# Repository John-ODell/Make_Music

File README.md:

Making Music with passive Buzzers by John O'Dell
--Update-- 12/4/2024 -> New Synth Update, Scroll Below for instructions. 

Arduino_Scale_Example

Items needed

    - Arduino uno (tested on r4)
    - Raspbery Pi Pico (Test on Pi Pico 2)
    - Passive buzzer module (two preffered and used in sketch)
    - Jumper Wire

Pin Outs

Buzzer 1
    - signal -> Pin 2
    - GND -> GND
    - VCC -> 3.3v

Buzzer 2

    - signal -> Pin 3
    - GND -> GND
    - VCC -> 3.3v

Download the Arduino IDE Platform https://www.arduino.cc/en/software

Open the sketch "arduino_scale_example"

    - Compile and write to your device
    - On Buzzer one C major scale with play with half notes in two onvtices
    - On Buzzer two C major scale will play with Whole notes in two octives

Python Example

Pin Outs

Buzzer 1
    - signal -> Pin 20
    - GND -> GND
    - VCC -> 3.3v

Buzzer 2

    - signal -> Pin 19
    - GND -> GND
    - VCC -> 3.3v

Download the Thonny IDE Platform https://thonny.org/
    
** Follow the Flash Instructions Below To install Micropython onto your Device **

Open the sketch "passive_buzzer_music_test"

    - Press the green arrow
    - On Buzzer one C major scale with play with half notes in two onvtices
    - On Buzzer two C major scale will play with Whole notes in two octives

TROUBLESHOOTING

    - Make sure that your wires are correct for sketch
    - You may get feedback from just signal wires, make sure vcc and ground are in
    - keep to 3.3v on the arduino
    - Some buzzer modules are not good enough quality
    - to increase or quite the noise, change the duty cycle
    - notation is based off 440A and modern tunings. 

** Flashing MicroPython **

    - Open Thonny
    - Navigate to the top left
     - click run
      - configure interpreter 
      - on the bottom right
        - install Micropython
            - Target Volume will be chosen
            - Micrpython Family (RP2 for Raspberry Pi/Your device Family)
            - Variant (Check the Manufacturer)
            - Version, Most recent
            - Install
    - Afer the flash is done exit out of the Interpreter Pages
    - Click on run again
        - Configuer Interpreter
        - "Which Kind of INterpreter should Thonny use"
            - Micropython for your model device (some models will be automatically dedectied)
        - "Port or WebREPL"
            - COMS(number)
            - This number may have changed from when you ran through this the first time.
            - Click Ok
    - On the Thonny home page, Click the Red stop Sign
    - In the Shell below, You will see your device.

---- Pi Pico Synth - 10 Key Bread Board Synth by John O'Dell ----
Updated 12/4/2024

Items needed

    - 10 Touch Input models (feel free to change the inputs, I found touch to be the best for input time, 10 inputs needed)
    - 2 Passive Buzzers (based on how loud you want your Synth to be)
    - Pi Pico 2 with Micropython
    - Thonny IDE
    - ~40 Jumper Wires
    - 2 Breadboards (Recommended for Button Placement but can be done with 1)

This Sketch requires your inputs to be accesseble at all times, please think about how you are wiring so there are not any false inputs.

Pin Outs 

    - All Modules will use a common 3.3v and GND
    - It is easiest to "pick a side" for each module
        - Touch inputs
            - VCC -> 3.3v
            - GND -> GND
            - S -> GPIO 16 - GPIO 22, GPIO 26-28 
                - 10 sequintial pins for easy orginization
        - Passive Buzzers
            - VCC -> 3.3v
            - GND -> GND
            - S -> GPIO 12 - GPIO 13
                - 2 sequintal pins for two buzzers, add more for more sound. I found two is good for personal playing.

Touch Button Example

This example is to make sure your inputs are working

    - open "touch_button.py" and press the green arrow
    - when you press a button in the serial monitor it will return a button has been pressed
    - Change the Pin number in the top the check if all your buttons are working

TROUBLESHOOTING

    - Make Sure you have not switched the VCC and the GND
    - The number is not the pin number but eh GPIO number, refer to the Raspberr Pi Pico pinout sheet

8 Key example

In this example We use 8 touch buttons and turn them into the "White keys" of a piano by assigning them each to a note of the C major scale.
We anchor this tuning based on A4 (fourth octive) at A 440hz. From this we can find the tuning of our different keys. We have a high sample rate for self regulation of Timing rather than a set BPM

    - Open "8_key.py" and press the green arrow
    - starting with the input assigned to GPIO 16, we play a major C scale.
    - In the serial monitor there will be a high refresh rate showing when a button is pressed along with the frequency associated with it

TROUBLESHOOTING

    - make sure you have VCC and GND correct
    - Make sure you are in the Correct GPIO pins
    - if wired in parrallel, there could be a power issue, wiring pin for pin I found has a better sound

--- Pi Pico Synth by John O'Dell ----

This is a mini Synth that has uses 10 touch inputs with passive buzzers to achieve two full ovtives of a piano/synth. 
8 Inputs are assigned the me C major scale, with one Input raising them a half step and another raising them an octive.
This is a fun exmperimental instrument that has a particular 8 bit sound to it.

    - Follow the main wiring diagram 
    - Open "mod_8_key.py" and press the green arrow
        - to play on boot, save the file to the Pi Pico device and name it "boot.py"
            - to get out of a boot cycle, refer to the  **Flashing MicroPython** Section
    
    - Feel Free to change the assigned tones to the keys to make a new set scale.
    - The modulating buttons can be changed as well in their current function, or a totally new one.
    
Practice Song:

    - (refer the the GPIO Pins)
        - |16 18 20|16 18 20|17 19 21|17 19 21|17 19 22|17 19 22|19 21 26|19 21 26|
    - (Refer to the Notes)
        -|C E G| C E G| D F A| D F A| D F B| D F B| E A C| E A C|

## PCB development

The first battery-powered Pico carrier is now an editable, routed KiCad project with removable Pico H sockets, ten touch controls, two buzzer module connectors and GPIO expansion. Electrical/board checks pass; exact-part fit, mechanical CAD and bench validation still hold fabrication. See [hardware/README.md](hardware/README.md) for the project and held review files.

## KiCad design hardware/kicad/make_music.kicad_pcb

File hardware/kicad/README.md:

# Editable Pico instrument carrier

Open `make_music.kicad_pro` in KiCad 10, then open the schematic. The project-local `MakeMusic.kicad_sym` library and `sym-lib-table` resolve all symbols. `fp-lib-table` registers socket, carrier and power libraries plus installed KiCad 10 `Connector_JST`, `Resistor_SMD`, `Capacitor_SMD` and `TestPoint` libraries. The schematic is the editable source of truth; do not regenerate it from the review PDF.

- `make_music.kicad_sch`: A3 root with two removable female sockets, ten touch/two buzzer cable headers, expansion, two reset pull-ups, twelve 100nF header bypass capacitors and C17/C18 10µF buzzer bulk capacitors.
- `battery_power.kicad_sch`: editable A3 child sheet with JST battery entry, upstream fuse, switch, TPS259474L protection and supporting passives/clamps; VSYS/GND connect through hierarchical ports.
- `make_music.kicad_pcb`: routed 48-part electrical carrier with 17 mounting holes, two ground pours and module/cassette references. C17/C18 and corrected 18650/H1 routing are integrated. Current checks and retained metadata warnings are in [PCB status](PCB_STATUS.md).
- `schematic-review.pdf`: readable two-page A3 schematic export, marked prototype review.
- `pico-socket-map.csv`: all 40 Pico physical pins mapped to local socket pins and carrier nets.
- `verify_connectivity.py`: checks every endpoint in a fresh XML netlist against the reviewed interface contract.
- `carrier-interfaces.md`: exact carrier parts, cable mapping, footprint evidence and placement/release gates.
- `power-integration.md`: native reference mapping, power parts, RPW/fuse/TVS geometry, validation and qualification gates.
- `../reviews/schematic.md`: verified facts, actual checks and unresolved design decisions.

J1 and J2 each use local pad numbers 1-20. J1 pin 1 is at the USB end; J2 pin 1 is at the opposite end. J2 pin 20 is beside USB. J1/J2 are assigned `MakeMusic:Samtec_SSQ-120-01-G-S_1x20_P2.54mm` as candidates. Place J1 pad 1 at USB and rotate J2 180 degrees relative to J1 so J2 pad 20 is at USB. This integration numbering supersedes the mechanical proposal's alternative right-row pad-1-at-USB convention; do not reverse the existing schematic nets to match that proposal.

J3-J14 carrier order is defined as 1=SIG, 2=3V3_OUT, 3=GND. Assigned Harwin headers are cable adapters; actual module pin order is mapped separately by label, and no module mounting geometry is claimed. J15 has the exact Harwin 16-way candidate and defined GPIO order. H1 is the underside JST PH battery harness, circuit1=BAT_PROT_PLUS/circuit2=GND; it does not put holder contacts or holes on the carrier. All **48 schematic physical components** have assigned footprints: **47 purchased parts** plus TP1's 2mm bare copper test pad. J1/J2 now store native SSQ-120-01-G-S MPN and Samtec datasheet fields; supplier BOMs need no socket-identity substitution. See [carrier interface contract](carrier-interfaces.md) for ST0238 cable permutation, reset bias, bulk-capacitor land evidence and local bypass placement. The selected inserted module is original non-wireless RP2040 Pico H SC0917 with fitted male headers; its electronics and the module drivers remain off-board/unmodeled. Cold-fit/engagement checks remain. The updated schematic passes native ERC with zero errors/warnings and the 166-endpoint contract; live PCB pad/identity checks now agree; four custom-field warnings remain reported.

Run from this directory (write generated logs/netlists outside the repository):

```sh
kicad-cli sch erc --severity-all --exit-code-violations --format json -o /tmp/make-music-erc.json make_music.kicad_sch
kicad-cli sch export netlist --format kicadxml -o /tmp/make-music-netlist.xml make_music.kicad_sch
python3 verify_connectivity.py /tmp/make-music-netlist.xml
kicad-cli sch export pdf -o schematic-review.pdf make_music.kicad_sch
```

The user permits firmware adaptation to confirmed touch polarity, including active-low. Confirm direct/momentary configuration and actual idle/touched levels first; the separate carrier_prototype.py firmware supports configurable active levels; no module polarity has been measured.

Revision-1 source path: protected-cell external + -> H1 circuit1 -> F1 -> BAT_FUSED_PLUS -> S1 common2; S1 throw3 -> BAT_SW_PLUS -> U2 IN5; U2 OUT6 -> VSYS/Pico physical39. S1 throw1 is NC (battery OFF). H1 circuit2 joins GND. Carrier series D1 is removed. D2 is a VSYS-to-GND shunt clamp; D3 is the bidirectional input TVS. TP1 only joins USB VBUS/Pico physical40. The Pico's internal USB diode/regulator remain off-board. See [native power integration](power-integration.md) for exact R3–R8/C13–C16 mapping and package evidence.

Battery OFF permits USB power. Remove the cell for external charging; no onboard charger is present. Source changes may reboot: stop playing and let the instrument restart before resuming. No polymer hold-up additions are fitted. Hardware UVLO/overload protection is implemented, while assembly-specific protection response, PCM thresholds, actual cell/holder fit and power/load/thermal validation remain open. Adopted limits are ≤0.70A battery branch, ≤350mA total3V3 including Pico, ≤250mA external3V3 and ≤100µF total VSYS capacitance including Pico. The user corrected the battery format to **18650** on 2026-10-09; the primary power/mechanical review owns updated exact cell/holder/charger choices. R1/R2 bias GP13/12 HIGH while pins are high impedance; firmware must idle HIGH and ST0238 startup/current/PWM still need testing. C1–C12 remain100nF at the carrier headers; native C5/C6 are retained and are unrelated to the removed power-document polymer C5/C6. C17/C18 add 10µF each at J13/J14 on 3V3_OUT; qualify effective capacitance and 3V3 startup/inrush.

The current held package includes C17/C18 and the corrected long18650
cassette/H1 move. Electrical integration and saved/refilled checks agree with
the source-bound exports. Native parity retains four metadata warnings; actual
pad nets, values and full footprint IDs agree. All drawing pages and actual
Gerber/drill whole/detail reviews are recorded. Current findings are in
PCB_STATUS.md. Complete exact-part fit, final mechanical CAD, bench/thermal
qualification and factory acceptance before manufacturing release. See
../assembly/FIT_CHECKLIST.md and ../manufacturing/README.md. The retired
export_review.py refuses to run; native exports use Konnect MCP.

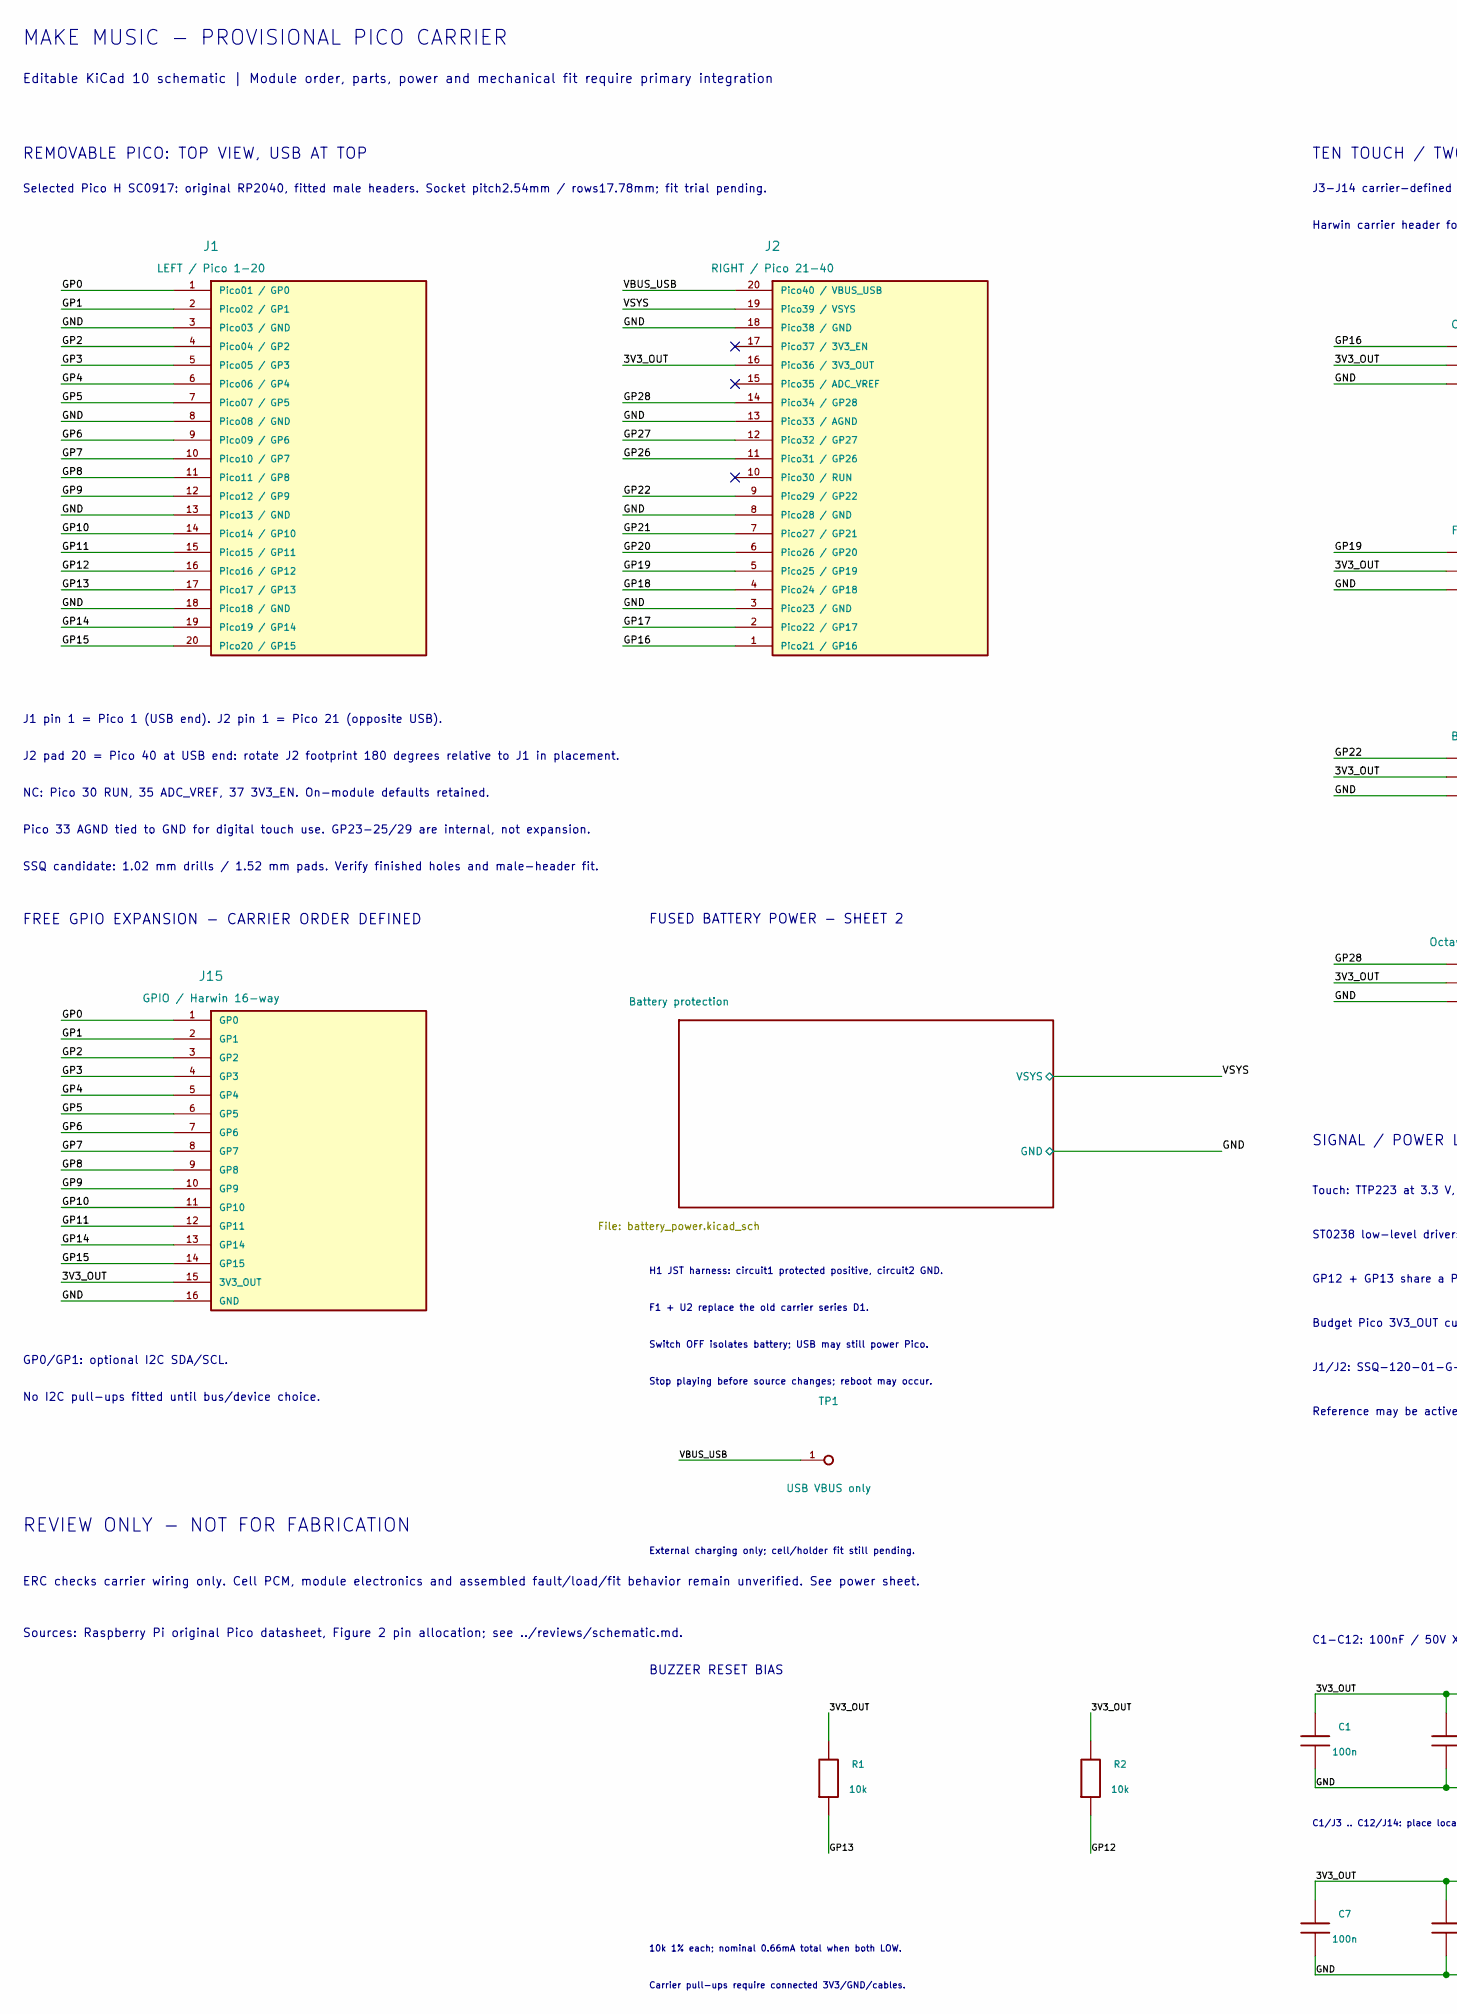
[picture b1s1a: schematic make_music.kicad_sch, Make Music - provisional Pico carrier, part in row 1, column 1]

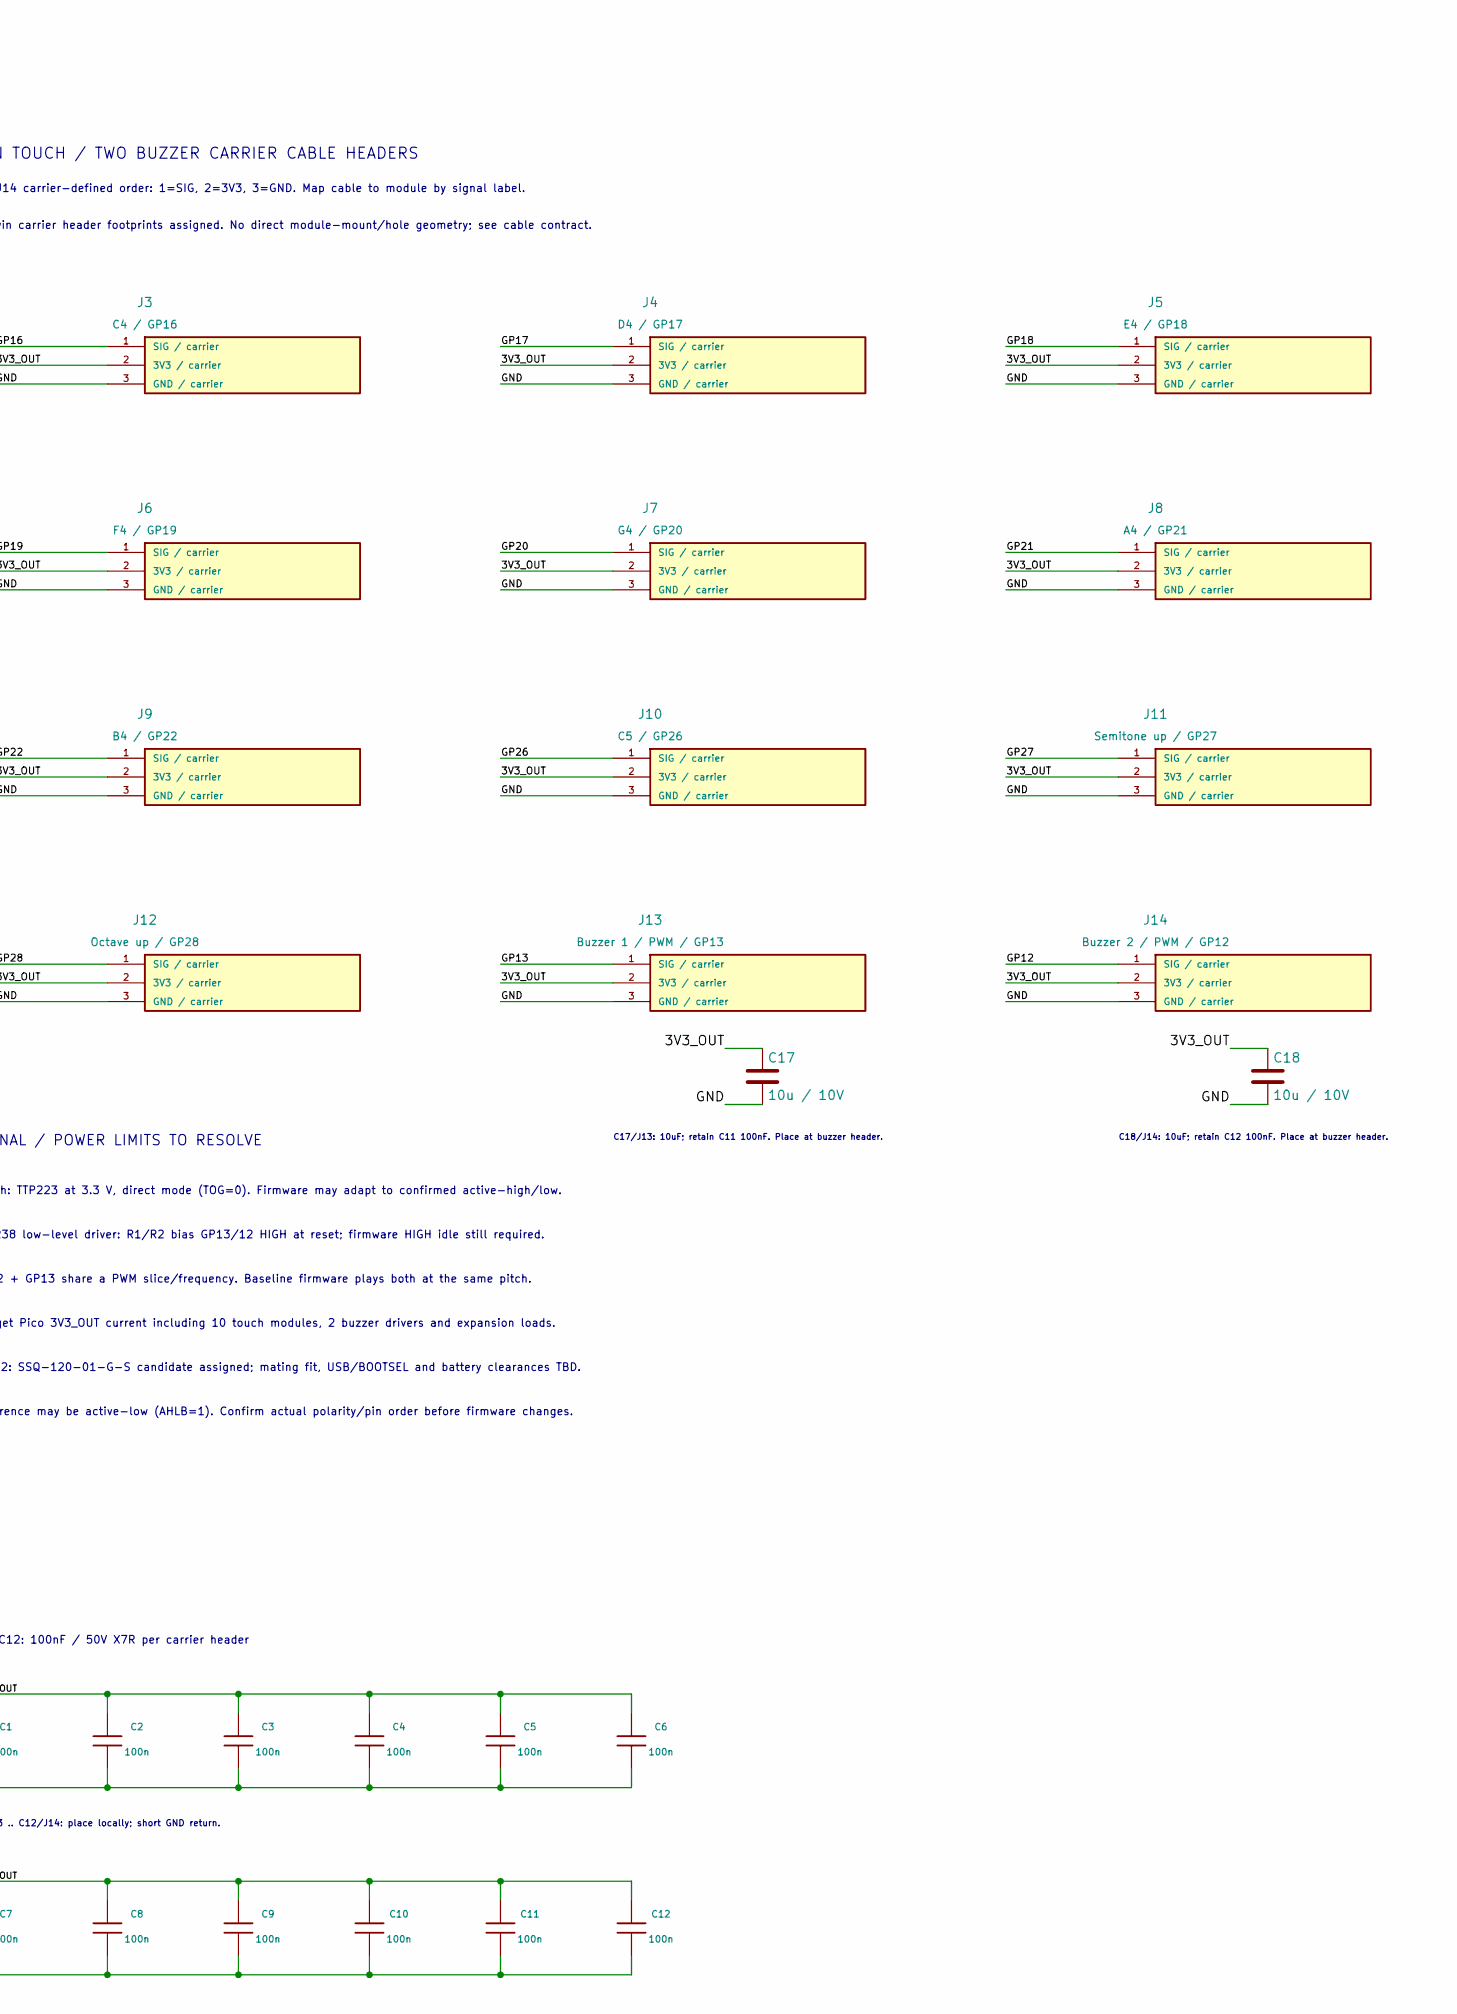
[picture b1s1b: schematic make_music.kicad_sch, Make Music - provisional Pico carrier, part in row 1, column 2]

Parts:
C1, C2, C3, C4, C5, C6, C7, C8, C9, C10, C11, C12: 100n; KEMET_C0603_1608_LevelB; MPN C0603C104K5RACTU
C17, C18: 10u / 10V; C_0805_2012Metric; MPN C2012X7R1A106K125AC
J1: LEFT / Pico 1-20; Samtec_SSQ-120-01-G-S_1x20_P2.54mm; MPN SSQ-120-01-G-S
J2: RIGHT / Pico 21-40; Samtec_SSQ-120-01-G-S_1x20_P2.54mm; MPN SSQ-120-01-G-S
J3: C4 / GP16; Harwin_M20-9990346_1x3_P2.54mm; MPN M20-9990346
J4: D4 / GP17; Harwin_M20-9990346_1x3_P2.54mm; MPN M20-9990346
J5: E4 / GP18; Harwin_M20-9990346_1x3_P2.54mm; MPN M20-9990346
J6: F4 / GP19; Harwin_M20-9990346_1x3_P2.54mm; MPN M20-9990346
J7: G4 / GP20; Harwin_M20-9990346_1x3_P2.54mm; MPN M20-9990346
J8: A4 / GP21; Harwin_M20-9990346_1x3_P2.54mm; MPN M20-9990346
J9: B4 / GP22; Harwin_M20-9990346_1x3_P2.54mm; MPN M20-9990346
J10: C5 / GP26; Harwin_M20-9990346_1x3_P2.54mm; MPN M20-9990346
J11: Semitone up / GP27; Harwin_M20-9990346_1x3_P2.54mm; MPN M20-9990346
J12: Octave up / GP28; Harwin_M20-9990346_1x3_P2.54mm; MPN M20-9990346
J13: Buzzer 1 / PWM / GP13; Harwin_M20-9990346_1x3_P2.54mm; MPN M20-9990346
J14: Buzzer 2 / PWM / GP12; Harwin_M20-9990346_1x3_P2.54mm; MPN M20-9990346
J15: GPIO / Harwin 16-way; Harwin_M20-9991646_1x16_P2.54mm; MPN M20-9991646
R1, R2: 10k; R_0603_1608Metric; MPN RC0603FR-0710KL
TP1: USB VBUS only; TestPoint_Pad_D2.0mm

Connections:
/3V3_OUT: C1.1, C2.1, C3.1, C4.1, C5.1, C6.1, C7.1, C8.1, C9.1, C10.1, C11.1, C12.1, C17.1, C18.1, J2.16 (Pico36 / 3V3_OUT), J3.2 (3V3 / carrier), J4.2 (3V3 / carrier), J5.2 (3V3 / carrier), J6.2 (3V3 / carrier), J7.2 (3V3 / carrier), J8.2 (3V3 / carrier), J9.2 (3V3 / carrier), J10.2 (3V3 / carrier), J11.2 (3V3 / carrier), J12.2 (3V3 / carrier), J13.2 (3V3 / carrier), J14.2 (3V3 / carrier), J15.15 (3V3_OUT), R1.1, R2.1
/GND: C1.2, C2.2, C3.2, C4.2, C5.2, C6.2, C7.2, C8.2, C9.2, C10.2, C11.2, C12.2, C17.2, C18.2, J1.3 (Pico03 / GND), J1.8 (Pico08 / GND), J1.13 (Pico13 / GND), J1.18 (Pico18 / GND), J2.3 (Pico23 / GND), J2.8 (Pico28 / GND), J2.13 (Pico33 / AGND), J2.18 (Pico38 / GND), J3.3 (GND / carrier), J4.3 (GND / carrier), J5.3 (GND / carrier), J6.3 (GND / carrier), J7.3 (GND / carrier), J8.3 (GND / carrier), J9.3 (GND / carrier), J10.3 (GND / carrier), J11.3 (GND / carrier), J12.3 (GND / carrier), J13.3 (GND / carrier), J14.3 (GND / carrier), J15.16 (GND); also elsewhere on the board
/GP0: J1.1 (Pico01 / GP0), J15.1 (GP0)
/GP1: J1.2 (Pico02 / GP1), J15.2 (GP1)
/GP2: J1.4 (Pico04 / GP2), J15.3 (GP2)
/GP3: J1.5 (Pico05 / GP3), J15.4 (GP3)
/GP4: J1.6 (Pico06 / GP4), J15.5 (GP4)
/GP5: J1.7 (Pico07 / GP5), J15.6 (GP5)
/GP6: J1.9 (Pico09 / GP6), J15.7 (GP6)
/GP7: J1.10 (Pico10 / GP7), J15.8 (GP7)
/GP8: J1.11 (Pico11 / GP8), J15.9 (GP8)
/GP9: J1.12 (Pico12 / GP9), J15.10 (GP9)
/GP10: J1.14 (Pico14 / GP10), J15.11 (GP10)
/GP11: J1.15 (Pico15 / GP11), J15.12 (GP11)
/GP12: J1.16 (Pico16 / GP12), J14.1 (SIG / carrier), R2.2
/GP13: J1.17 (Pico17 / GP13), J13.1 (SIG / carrier), R1.2
/GP14: J1.19 (Pico19 / GP14), J15.13 (GP14)
/GP15: J1.20 (Pico20 / GP15), J15.14 (GP15)
/GP16: J2.1 (Pico21 / GP16), J3.1 (SIG / carrier)
/GP17: J2.2 (Pico22 / GP17), J4.1 (SIG / carrier)
/GP18: J2.4 (Pico24 / GP18), J5.1 (SIG / carrier)
/GP19: J2.5 (Pico25 / GP19), J6.1 (SIG / carrier)
/GP20: J2.6 (Pico26 / GP20), J7.1 (SIG / carrier)
/GP21: J2.7 (Pico27 / GP21), J8.1 (SIG / carrier)
/GP22: J2.9 (Pico29 / GP22), J9.1 (SIG / carrier)
/GP26: J2.11 (Pico31 / GP26), J10.1 (SIG / carrier)
/GP27: J2.12 (Pico32 / GP27), J11.1 (SIG / carrier)
/GP28: J2.14 (Pico34 / GP28), J12.1 (SIG / carrier)
/VBUS_USB: J2.20 (Pico40 / VBUS_USB), TP1.1
/VSYS: J2.19 (Pico39 / VSYS); also elsewhere on the board

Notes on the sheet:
MAKE MUSIC - PROVISIONAL PICO CARRIER
Editable KiCad 10 schematic | Module order, parts, power and mechanical fit require primary integration
REMOVABLE PICO: TOP VIEW, USB AT TOP
Selected Pico H SC0917: original RP2040, fitted male headers. Socket pitch2.54mm / rows17.78mm; fit trial pending.
J1 pin 1 = Pico 1 (USB end). J2 pin 1 = Pico 21 (opposite USB).
J2 pad 20 = Pico 40 at USB end: rotate J2 footprint 180 degrees relative to J1 in placement.
NC: Pico 30 RUN, 35 ADC_VREF, 37 3V3_EN. On-module defaults retained.
Pico 33 AGND tied to GND for digital touch use. GP23-25/29 are internal, not expansion.
FREE GPIO EXPANSION - CARRIER ORDER DEFINED
GP0/GP1: optional I2C SDA/SCL.
No I2C pull-ups fitted until bus/device choice.
TEN TOUCH / TWO BUZZER CARRIER CABLE HEADERS
J3-J14 carrier-defined order: 1=SIG, 2=3V3, 3=GND. Map cable to module by signal label.
Harwin carrier header footprints assigned. No direct module-mount/hole geometry; see cable contract.
SIGNAL / POWER LIMITS TO RESOLVE
Touch: TTP223 at 3.3 V, direct mode (TOG=0). Firmware may adapt to confirmed active-high/low.
ST0238 low-level driver: R1/R2 bias GP13/12 HIGH at reset; firmware HIGH idle still required.
GP12 + GP13 share a PWM slice/frequency. Baseline firmware plays both at the same pitch.
Budget Pico 3V3_OUT current including 10 touch modules, 2 buzzer drivers and expansion loads.
J1/J2: SSQ-120-01-G-S candidate assigned; mating fit, USB/BOOTSEL and battery clearances TBD.
REVIEW ONLY - NOT FOR FABRICATION
ERC checks carrier wiring only. Cell PCM, module electronics and assembled fault/load/fit behavior remain unverified. See power sheet.
Sources: Raspberry Pi original Pico datasheet, Figure 2 pin allocation; see ../reviews/schematic.md.
Reference may be active-low (AHLB=1). Confirm actual polarity/pin order before firmware changes.
SSQ candidate: 1.02 mm drills / 1.52 mm pads. Verify finished holes and male-header fit.
BUZZER RESET BIAS
10k 1% each; nominal 0.66mA total when both LOW.
Carrier pull-ups require connected 3V3/GND/cables.
C1-C12: 100nF / 50V X7R per carrier header
C1/J3 .. C12/J14: place locally; short GND return.
FUSED BATTERY POWER - SHEET 2
H1 JST harness: circuit1 protected positive, circuit2 GND.
F1 + U2 replace the old carrier series D1.
Switch OFF isolates battery; USB may still power Pico.
Stop playing before source changes; reboot may occur.
External charging only; cell/holder fit still pending.
C17/J13: 10uF; retain C11 100nF. Place at buzzer header.
C18/J14: 10uF; retain C12 100nF. Place at buzzer header.

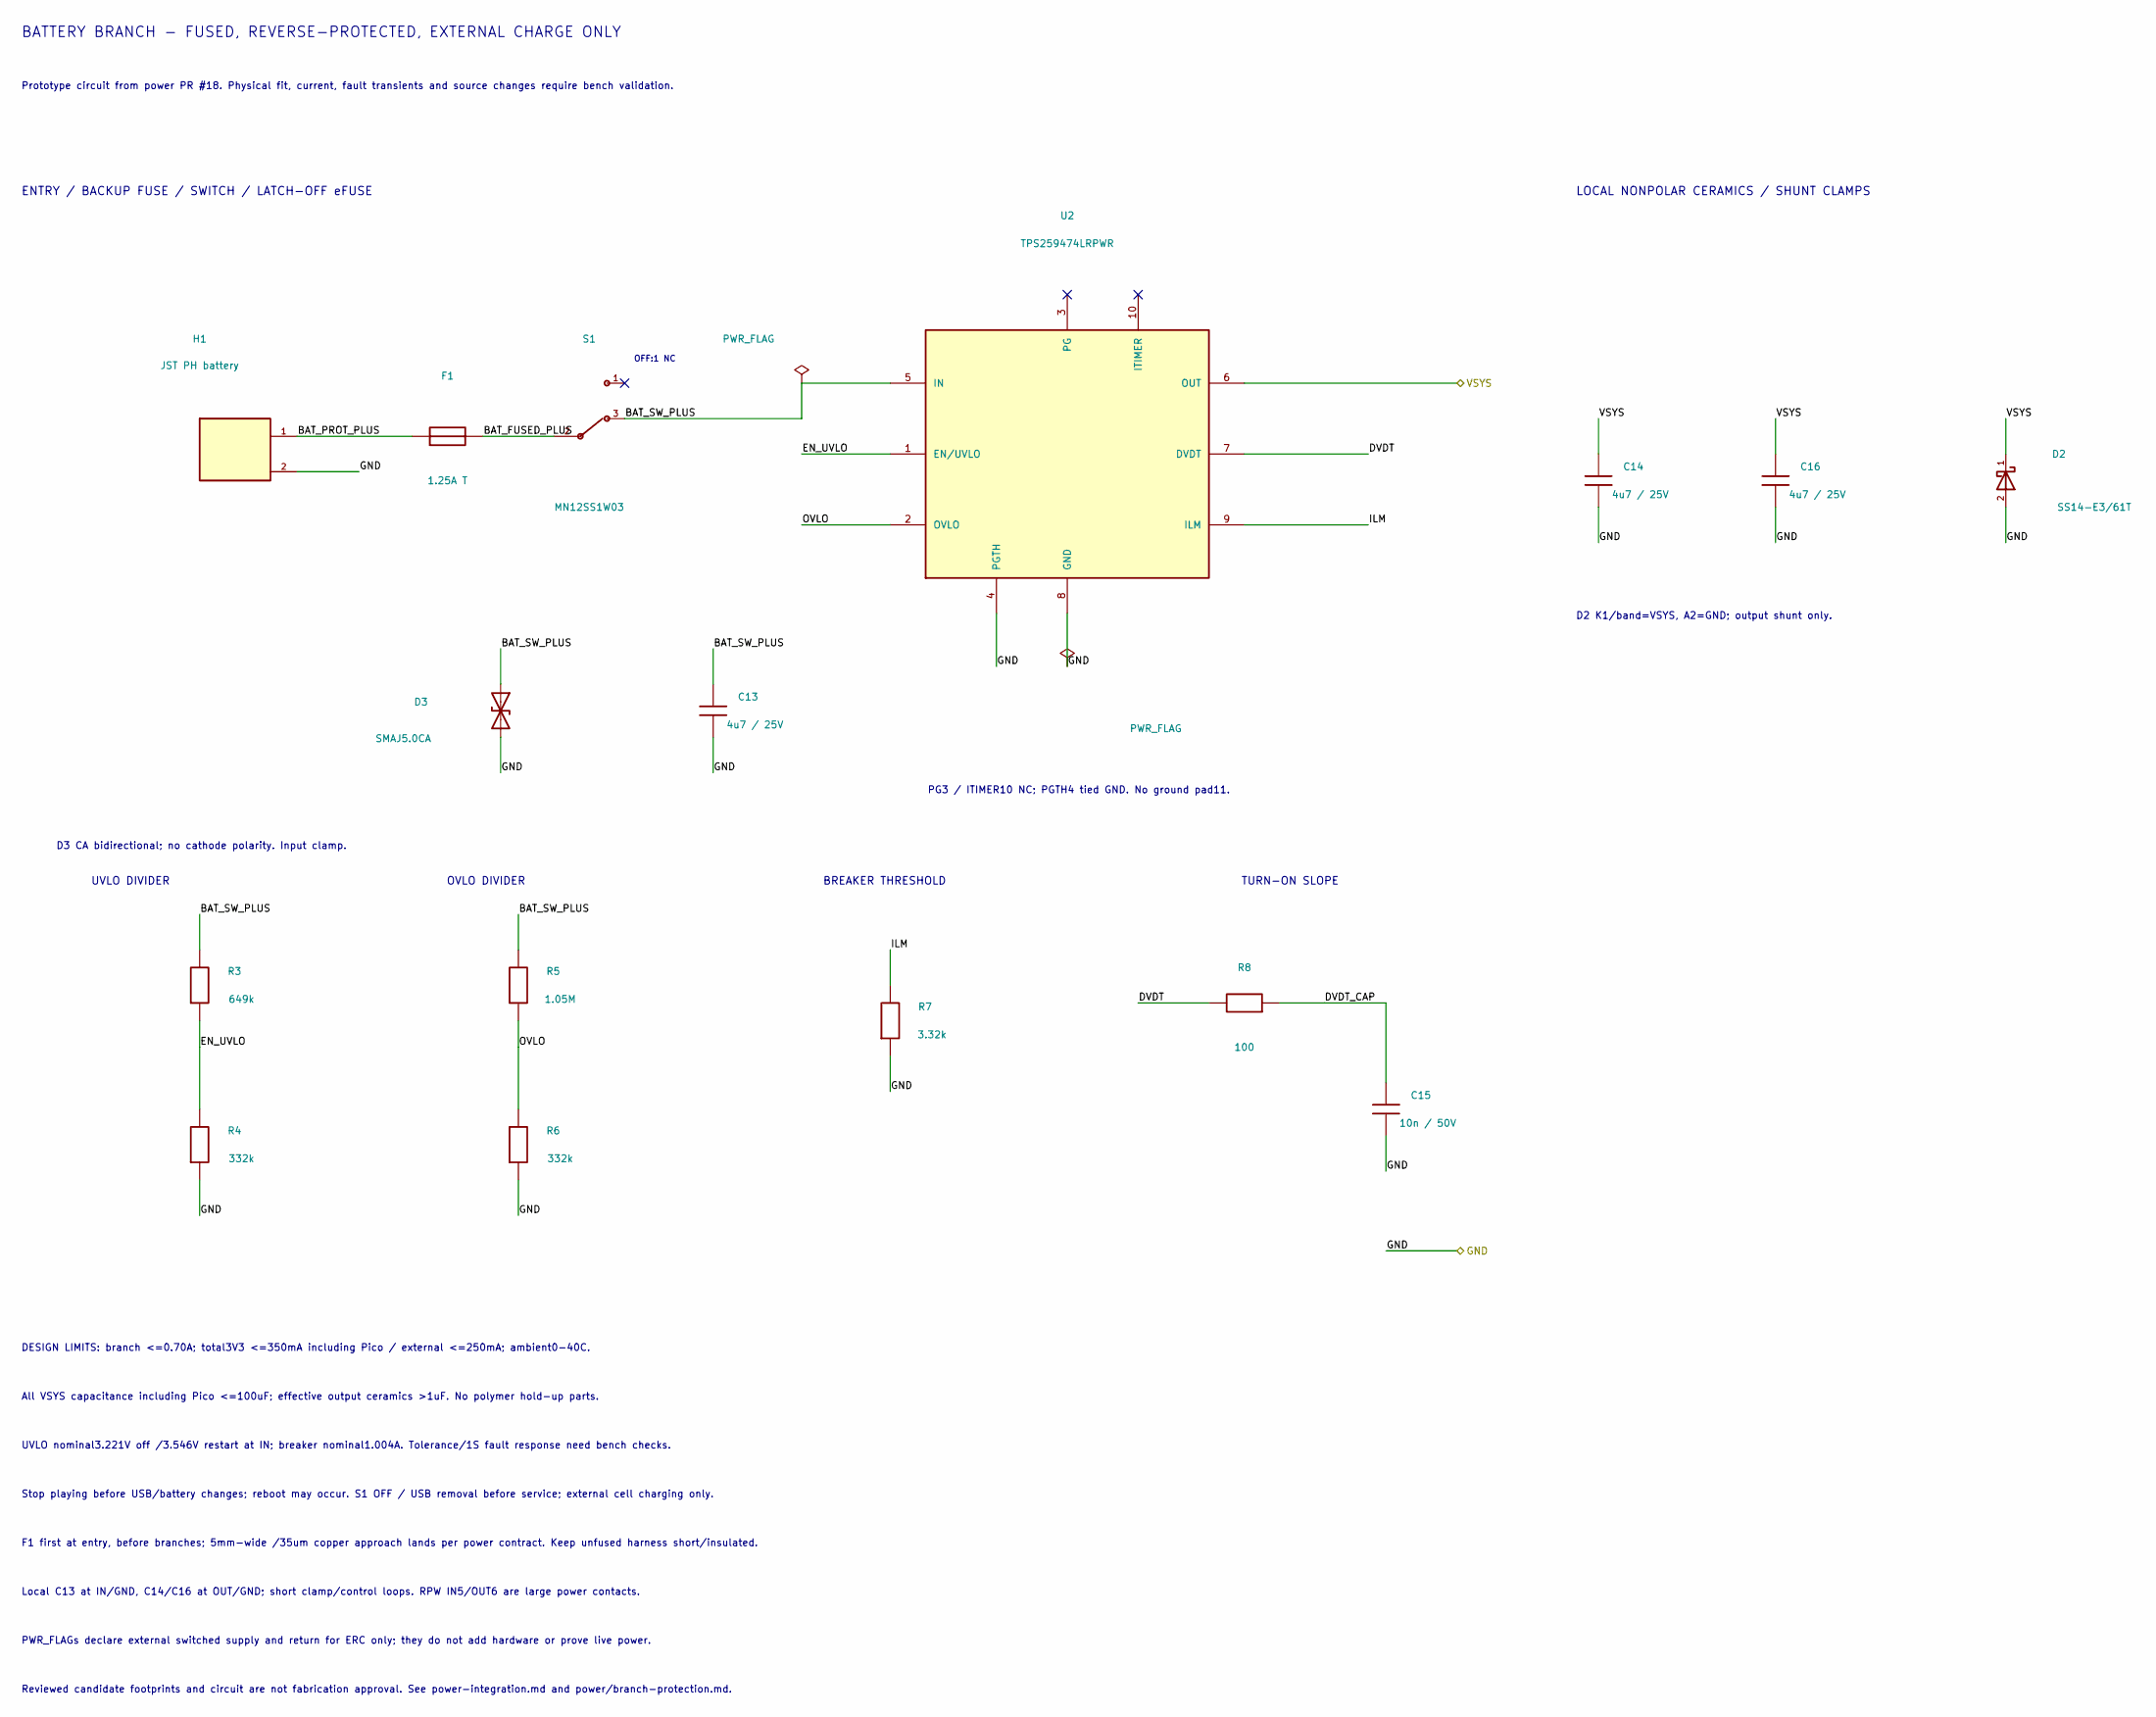
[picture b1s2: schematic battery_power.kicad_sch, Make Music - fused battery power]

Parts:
C13, C14, C16: 4u7 / 25V; C_0805_2012Metric; MPN C2012X7R1E475K125AB
C15: 10n / 50V; C_0603_1608Metric; MPN C1608C0G1H103J080AA
D2: SS14-E3/61T; Vishay_SS14_SMA_K1_A2; MPN SS14-E3/61T
D3: SMAJ5.0CA; Littelfuse_SMAJ5-0CA_DO-214AC; MPN SMAJ5.0CA
F1: 1.25A T; Schurter_UMT-H_3403-0275-23; MPN 3403.0275.23
H1: JST PH battery; JST_PH_B2B-PH-K_1x02_P2.00mm_Vertical; MPN B2B-PH-K-S(LF)(SN)
R3: 649k; R_0603_1608Metric; MPN RC0603FR-07649KL
R4, R6: 332k; R_0603_1608Metric; MPN RC0603FR-07332KL
R5: 1.05M; R_0603_1608Metric; MPN RC0603FR-071M05L
R7: 3.32k; R_0603_1608Metric; MPN RC0603FR-073K32L
R8: 100; R_0603_1608Metric; MPN RC0603FR-07100RL
S1: MN12SS1W03; NKK_MN12SS1W03_TerminalPattern_Candidate; MPN MN12SS1W03
U2: TPS259474LRPWR; TI_RPW0010A_TPS259474_2x2mm; MPN TPS259474LRPWR

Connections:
/Battery protection/BAT_FUSED_PLUS: F1.2, S1.2 (COM)
/Battery protection/BAT_PROT_PLUS: F1.1, H1.1 (PROTECTED_PLUS)
/Battery protection/BAT_SW_PLUS: C13.1, D3.1 (A1), R3.1, R5.1, S1.3 (BAT_ON), U2.5 (IN)
/Battery protection/DVDT: R8.1, U2.7 (DVDT)
/Battery protection/DVDT_CAP: C15.1, R8.2
/Battery protection/EN_UVLO: R3.2, R4.1, U2.1 (EN/UVLO)
/Battery protection/ILM: R7.1, U2.9 (ILM)
/Battery protection/OVLO: R5.2, R6.1, U2.2 (OVLO)
/GND: C13.2, C14.2, C15.2, C16.2, D2.2 (A), D3.2 (A2), H1.2 (PROTECTED_MINUS), R4.2, R6.2, R7.2, U2.4 (PGTH), U2.8 (GND); also elsewhere on the board
/VSYS: C14.1, C16.1, D2.1 (K), U2.6 (OUT); also elsewhere on the board

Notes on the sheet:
BATTERY BRANCH - FUSED, REVERSE-PROTECTED, EXTERNAL CHARGE ONLY
Prototype circuit from power PR #18. Physical fit, current, fault transients and source changes require bench validation.
ENTRY / BACKUP FUSE / SWITCH / LATCH-OFF eFUSE
OFF:1 NC
PG3 / ITIMER10 NC; PGTH4 tied GND. No ground pad11.
LOCAL NONPOLAR CERAMICS / SHUNT CLAMPS
D2 K1/band=VSYS, A2=GND; output shunt only.
D3 CA bidirectional; no cathode polarity. Input clamp.
UVLO DIVIDER
OVLO DIVIDER
BREAKER THRESHOLD
TURN-ON SLOPE
DESIGN LIMITS: branch <=0.70A; total3V3 <=350mA including Pico / external <=250mA; ambient0-40C.
All VSYS capacitance including Pico <=100uF; effective output ceramics >1uF. No polymer hold-up parts.
UVLO nominal3.221V off /3.546V restart at IN; breaker nominal1.004A. Tolerance/1S fault response need bench checks.
Stop playing before USB/battery changes; reboot may occur. S1 OFF / USB removal before service; external cell charging only.
F1 first at entry, before branches; 5mm-wide /35um copper approach lands per power contract. Keep unfused harness short/insulated.
Local C13 at IN/GND, C14/C16 at OUT/GND; short clamp/control loops. RPW IN5/OUT6 are large power contacts.
PWR_FLAGs declare external switched supply and return for ERC only; they do not add hardware or prove live power.
Reviewed candidate footprints and circuit are not fabrication approval. See power-integration.md and power/branch-protection.md.

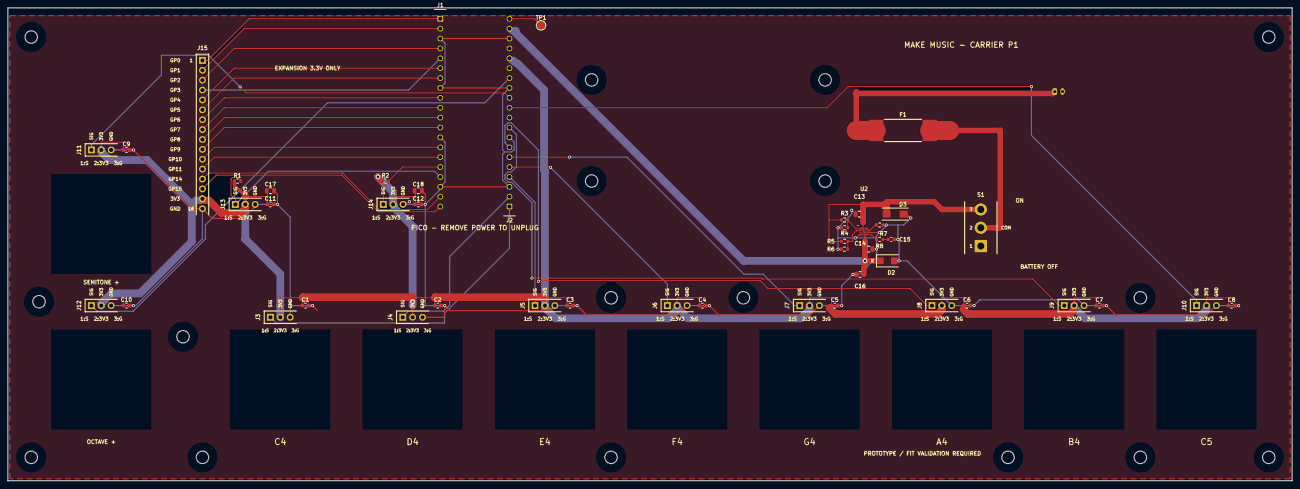
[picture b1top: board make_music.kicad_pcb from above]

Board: 2 copper layers, 330.0 x 121.5 mm, 65 parts (1 on the bottom side), 38 nets.

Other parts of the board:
MH1, MH2, MH3, MH4, MH5, MH6, MH7, MH8, MH9, MH10, MH11, MH12, MH13, MH14, MH15, MH16, MH17: MountingHole_3.2mm_M3

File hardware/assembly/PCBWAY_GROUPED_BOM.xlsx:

|  |  | Make Music P1 — 5 boards Carrier BOM: quantities per board
Item # | *Designator | *Qty | Manufacturer | *Mfg Part # | Description / Value | *Package/Footprint | Type | Your Instructions / Notes
1 | C1, C2, C3, C4, C5, C6, C7, C8, C9, C10, C11, C12 | 12 | KEMET | C0603C104K5RACTU | 100n | MakeMusicCarrier:KEMET_C0603_1608_LevelB | SMD | Top side. Supply and solder. No substitutions without approval.
2 | C13, C14, C16 | 3 | TDK | C2012X7R1E475K125AB | 4u7 / 25V | Capacitor_SMD:C_0805_2012Metric | SMD | Top side. Supply and solder. No substitutions without approval.
3 | C15 | 1 | TDK | C1608C0G1H103J080AA | 10n / 50V | Capacitor_SMD:C_0603_1608Metric | SMD | Top side. Supply and solder. No substitutions without approval.
4 | C17, C18 | 2 | TDK | C2012X7R1A106K125AC | 10u / 10V | Capacitor_SMD:C_0805_2012Metric | SMD | Top side. Supply and solder. No substitutions without approval.
5 | D2 | 1 | Vishay | SS14-E3/61T | SS14-E3/61T | MakeMusicCarrier:Vishay_SS14_SMA_K1_A2 | SMD | Top side. Supply and solder. No substitutions without approval.
6 | D3 | 1 | Littelfuse | SMAJ5.0CA | SMAJ5.0CA | MakeMusicPower:Littelfuse_SMAJ5-0CA_DO-214AC | SMD | Top side. Supply and solder. No substitutions without approval.
7 | F1 | 1 | SCHURTER | 3403.0275.23 | 1.25A T | MakeMusicPower:Schurter_UMT-H_3403-0275-23 | SMD | Top side. Supply and solder. No substitutions without approval.
8 | H1 | 1 | JST | B2B-PH-K-S(LF)(SN) | JST PH battery | Connector_JST:JST_PH_B2B-PH-K_1x02_P2.00mm_Vertical | thru-hole | Bottom side. Supply and solder. No substitutions without approval.
9 | J1, J2 | 2 | Samtec | SSQ-120-01-G-S | 20-pin female Pico socket, 2.54 mm pitch | MakeMusic:Samtec_SSQ-120-01-G-S_1x20_P2.54mm | thru-hole | Top side. Supply and solder. No substitutions without approval.
10 | J3, J4, J5, J6, J7, J8, J9, J10, J11, J12, J13, J14 | 12 | Harwin | M20-9990346 | 3-pin vertical male header, 2.54 mm pitch | MakeMusicCarrier:Harwin_M20-9990346_1x3_P2.54mm | thru-hole | Top side. Supply and solder. No substitutions without approval.
11 | J15 | 1 | Harwin | M20-9991646 | GPIO / Harwin 16-way | MakeMusicCarrier:Harwin_M20-9991646_1x16_P2.54mm | thru-hole | Top side. Supply and solder. No substitutions without approval.
12 | R1, R2 | 2 | Yageo | RC0603FR-0710KL | 10k | Resistor_SMD:R_0603_1608Metric | SMD | Top side. Supply and solder. No substitutions without approval.
13 | R3 | 1 | Yageo | RC0603FR-07649KL | 649k | Resistor_SMD:R_0603_1608Metric | SMD | Top side. Supply and solder. No substitutions without approval.
14 | R4, R6 | 2 | Yageo | RC0603FR-07332KL | 332k | Resistor_SMD:R_0603_1608Metric | SMD | Top side. Supply and solder. No substitutions without approval.
15 | R5 | 1 | Yageo | RC0603FR-071M05L | 1.05M | Resistor_SMD:R_0603_1608Metric | SMD | Top side. Supply and solder. No substitutions without approval.
16 | R7 | 1 | Yageo | RC0603FR-073K32L | 3.32k | Resistor_SMD:R_0603_1608Metric | SMD | Top side. Supply and solder. No substitutions without approval.
17 | R8 | 1 | Yageo | RC0603FR-07100RL | 100 | Resistor_SMD:R_0603_1608Metric | SMD | Top side. Supply and solder. No substitutions without approval.
18 | S1 | 1 | NKK | MN12SS1W03 | MN12SS1W03 | MakeMusicCarrier:NKK_MN12SS1W03_TerminalPattern_Candidate | thru-hole | Top side. Supply and solder. No substitutions without approval.
19 | U2 | 1 | Texas Instruments | TPS259474LRPWR | TPS259474LRPWR | MakeMusicPower:TI_RPW0010A_TPS259474_2x2mm | SMD | Top side. Supply and solder. No substitutions without approval.
QUOTE ONLY. No fabrication or assembly release. Qty is per board; batch quantit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
Carrier only: 47 components per board (30 SMD + 17 thru-hole), 235 for five. H1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
Complete-instrument modules, Pico H, battery/holder, harnesses, mechanics and t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
Source: reviewed carrier BOM, revision 0d6191a0e0217e7140bbceed22aa4e59db78747e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

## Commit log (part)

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2024-12-04 Add Synth
